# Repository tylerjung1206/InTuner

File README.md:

# InTuner
Welcome to my files for InTuner!

- To see the finalized code for the embedded system, check out main.cpp (located in final_code/src/main.cpp)
- To see my schematic, PCB, and CAD files, check out the schematic:pcb:cad folder. (You may need Eagle and Fusion installed to open them). An image for the manufacturer for the PCB is also there as a png file.

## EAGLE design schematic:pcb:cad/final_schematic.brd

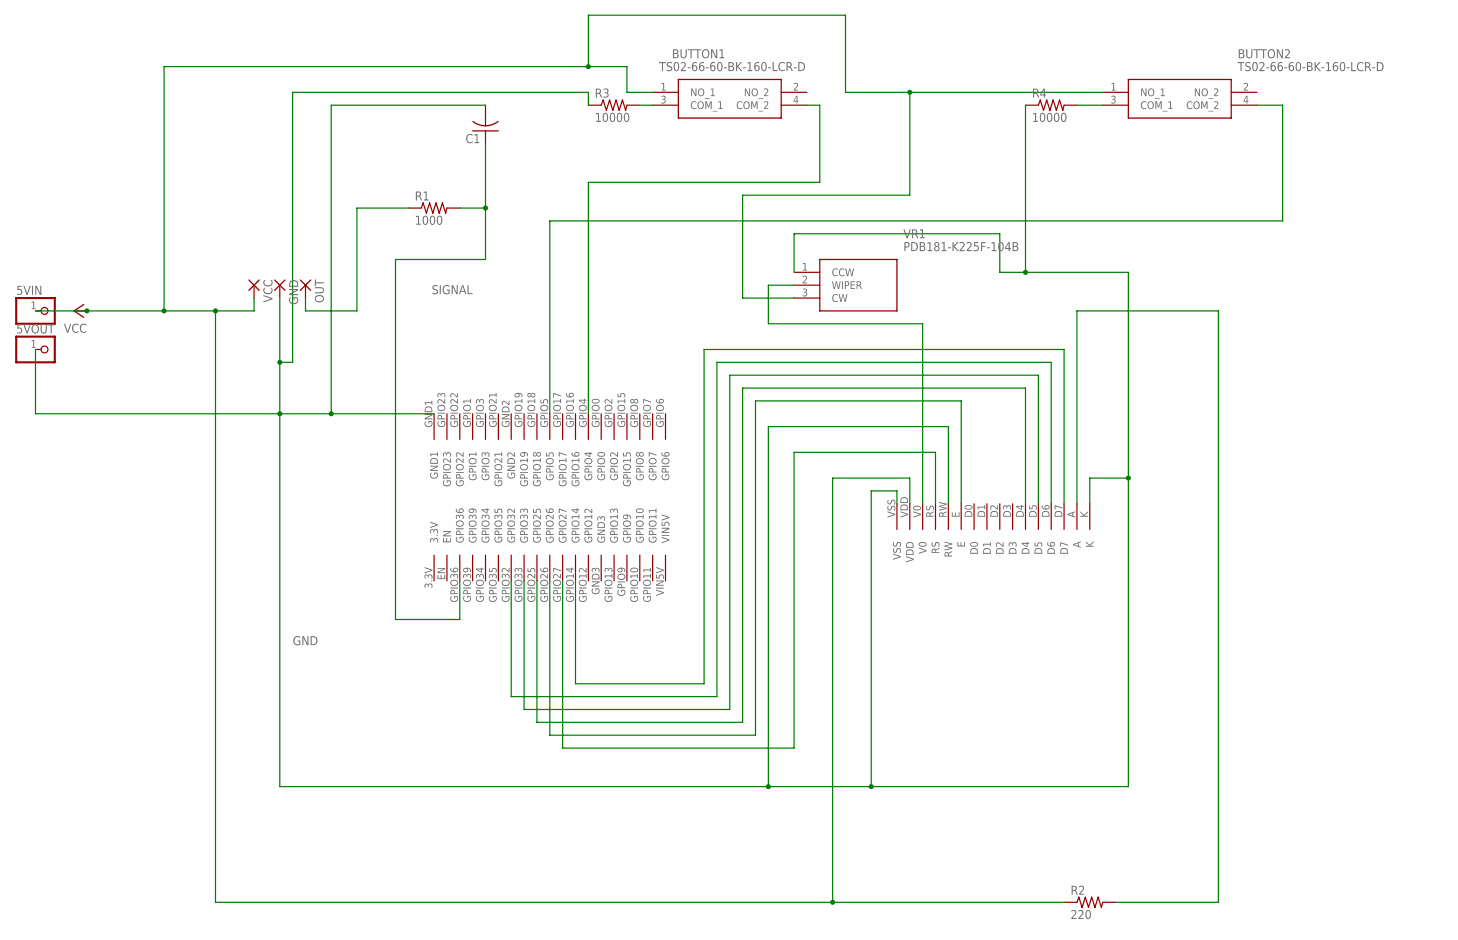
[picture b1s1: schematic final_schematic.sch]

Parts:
5VIN, 5VOUT: PINHD-1X1; 1X01
BUTTON1, BUTTON2: TS02-66-60-BK-160-LCR-D; TS026660BK160LCRD
C1: C-USC0805; C0805
GND: 1,6/0,8
OUT: 1,6/0,8
R1: 1000; R0805
R2: 220; R0805
R3, R4: 10000; R0805
U$1: HILETGO
U$2: LCD
VCC: 1,6/0,8
VR1: PDB181-K225F-104B; PDB181K225F104B

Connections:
GND: 5VOUT.1, C1.2, GND.1, R3.1, R4.1, U$1.GND1, U$2.K, U$2.RW, U$2.VSS, VR1.1 (CCW)
unnamed: BUTTON1.4 (COM_2), U$1.GPIO4
unnamed: OUT.1, R1.1
unnamed: U$1.GPIO27, U$2.RS
unnamed: U$1.GPIO33, U$2.D5
unnamed: U$1.GPIO26, U$2.E
unnamed: U$1.GPIO25, U$2.D4
unnamed: U$1.GPIO32, U$2.D6
unnamed: U$1.GPIO14, U$2.D7
unnamed: R2.2, U$2.A
unnamed: BUTTON1.3 (COM_1), R3.2
unnamed: BUTTON2.3 (COM_1), R4.2
unnamed: BUTTON2.4 (COM_2), U$1.GPIO5
unnamed: U$2.V0, VR1.2 (WIPER)
SIGNAL: C1.1, R1.2, U$1.GPIO36
VCC: 5VIN.1, BUTTON1.1 (NO_1), BUTTON2.1 (NO_1), R2.1, U$2.VDD, VCC.1, VR1.3 (CW)

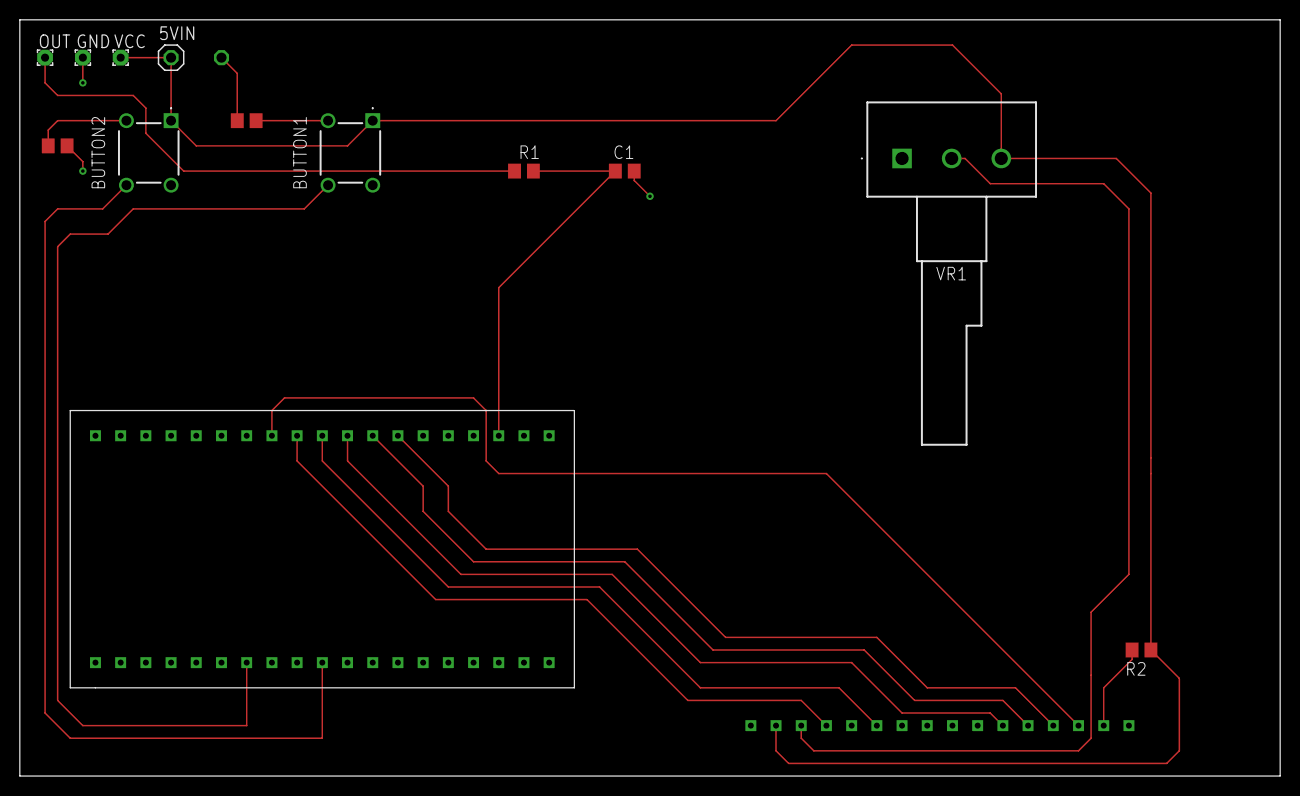
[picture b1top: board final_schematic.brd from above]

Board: 2 copper layers, 127.0 x 76.2 mm, 15 parts (1 on the bottom side), 16 nets.

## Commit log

2025-05-21 Clean initial commit without large history
2025-05-21 Initial commit without .wav files
2025-05-21 checked fft library
2025-05-22 5/21
2025-05-22 Ignore all PDFs
2025-05-22 Ignore and remove tracked PDFs
2025-05-22 Commit all changes excluding PDFs
2025-05-23 added spice drawing
2025-05-23 c++ code
2025-05-24 microcontroller files
2025-05-26 transform and feedback mode methods progress
2025-05-27 double stops
2025-05-29 data pipeline
2025-05-30 testing integration + file rearranging
2025-05-30 check
2025-06-02 began final code
2025-06-08 big progress
2025-06-09 finalized code with performance mode
2025-06-19 physical design files
2025-06-24 reorganized files
2025-06-24 new files
2025-06-24 unneccesary
2025-06-24 delete
2025-06-24 added to readme
